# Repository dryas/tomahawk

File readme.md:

# Tomahawk
Tomahawk is a fully open source hardware Bitcoin ASIC miner. It is based on the ideas of Bitaxe by Skot and the Open Source Miners United but a complete redesign with some different components. It includes a BM1366 ASIC which is also used in the Antminer S19XP.

DO NOT USE - WORK IN PROGRESS!

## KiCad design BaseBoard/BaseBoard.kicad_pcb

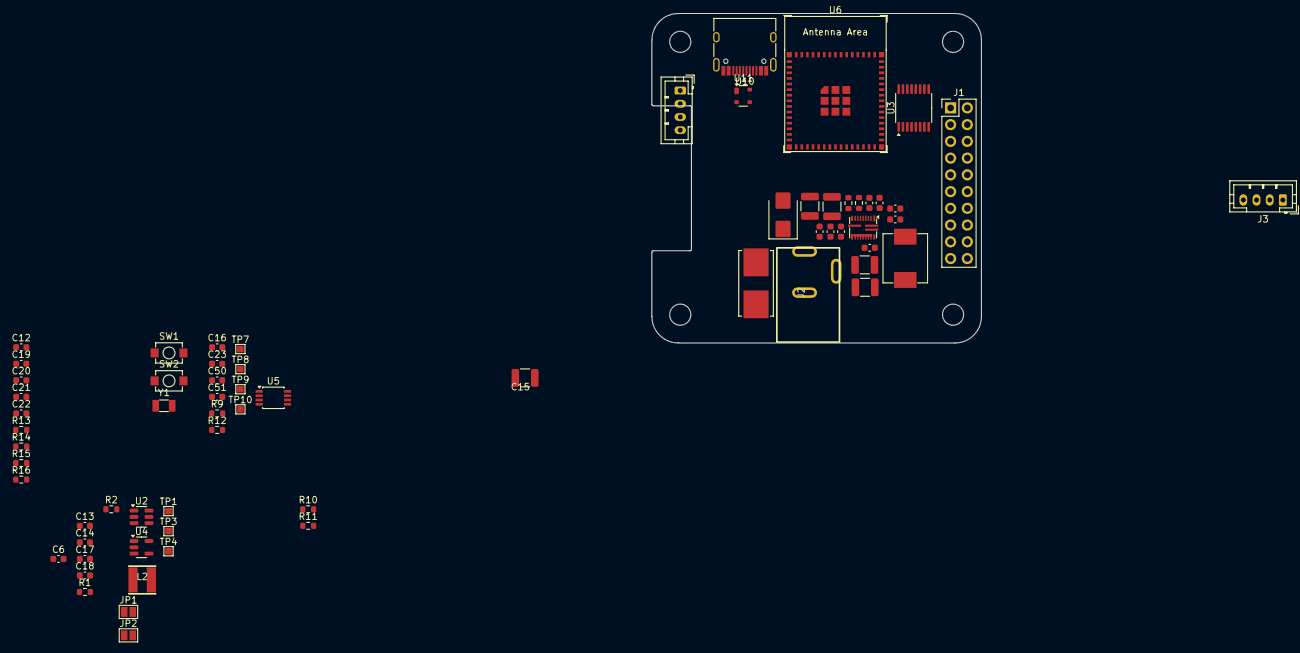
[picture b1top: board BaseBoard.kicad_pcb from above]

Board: 4 copper layers, 50.0 x 50.0 mm, 71 parts (0 on the bottom side), 39 nets, no tracks yet.

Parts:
C1, C2: 22uF; C_1210_3225Metric
C3, C4, C5, C12, C17: 1uF; C_0603_1608Metric
C6, C18: 4.7uF; C_0603_1608Metric
C7: 2.2uF; C_0603_1608Metric
C8: 120nF; C_0603_1608Metric
C9, C13, C16, C22, C23, C50: 100nF; C_0603_1608Metric
C10, C11: 100uF / 6,3V; C_1210_3225Metric
C14: 47pF; C_0603_1608Metric
C15: 47uF; C_1210_3225Metric
C19, C20: 6.8pF; C_0603_1608Metric
C21: 10uF; C_0603_1608Metric
C51: 470pF; C_0603_1608Metric
D1: SMBJ12A; D_SMB
F1: 2A; Fuseholder_Littelfuse_Nano2_154x
H1, H2, H3, H4: MountingHole; MountingHole_3.2mm_M3
J1: Conn_02x10_Odd_Even; PinHeader_2x10_P2.54mm_Vertical
J2: 54-00167
J3: SSD1306 OLED Display; JST_PH_B4B-PH-K_1x04_P2.00mm_Vertical
J4: FAN; JST_PH_B4B-PH-K_1x04_P2.00mm_Vertical
JP1, JP2: SolderJumper-2_P1.3mm_Open_Pad1.0x1.5mm
L1: 200nH / 23A; IND-SMD_L7.3-W6.6
L2: 6.8uH; IND-SMD_L4.1-W4.1
R1: 100k/1%; R_0603_1608Metric
R2: 22.1k/1%; R_0603_1608Metric
R3: 60.4k; C_0603_1608Metric
R4: 4.02k/1%; C_0603_1608Metric
R6: 10.7k/1%; R_0603_1608Metric
R7: 10k/1%; R_0603_1608Metric
R9, R12, R13, R14, R15, R16: 4.7k; R_0603_1608Metric
R10, R11: 5.1K; R_0603_1608Metric
SW1, SW2: SW_Push; TS-1088R-02526
TP1: +1.2V; TestPoint_Pad_1.0x1.0mm
TP3: +3.3V; TestPoint_Pad_1.0x1.0mm
TP4: +0.8V; TestPoint_Pad_1.0x1.0mm
TP7: TEMP_P; TestPoint_Pad_1.0x1.0mm
TP8: TEMP_N; TestPoint_Pad_1.0x1.0mm
TP9: FAN_PWM; TestPoint_Pad_1.0x1.0mm
TP10: FAN_TACH; TestPoint_Pad_1.0x1.0mm
U1: TPS548A28
U2: TPS54202DDC; SOT-23-6
U3: SN74AVC4T774; TSSOP-16_4.4x5mm_P0.65mm
U4: RT9078N-08GJ5; TSOT-23-5
U5: EMC2101; TSSOP-8_3x3mm_P0.65mm
U6: ESP32-S3-MINI-1
U10: USB Type C; USB_C_Receptacle_HRO_TYPE-C-31-M-12
U11: PRTR5V0U2X; SOT-143
Y1: 32.768kHz; Crystal_SMD_3215-2Pin_3.2x1.5mm

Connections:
+1V2: J1.15, J1.16, J1.17, J1.18, J1.19, J1.20
/IO/+1V2: C16.2, U3.7 (DIR3), U3.8 (DIR4), U3.16 (VCCA)
/IO/+3V3: C23.2, C50.2, R9.2, R12.2, U3.15 (VCCB), U5.1 (VDD)
/IO/FAN_PWM: R9.1, TP9.1, U5.4 (FAN)
/IO/FAN_TACH: R12.1, TP10.1, U5.6 (ALERT/TACH)
/IO/TEMP_N: C51.1, TP8.1, U5.3 (DN)
/IO/TEMP_P: C51.2, TP7.1, U5.2 (DP)
/MPU/+1V2: JP1.2 (B), R16.2
/MPU/+3v3: C17.2, C21.2, C22.2, J3.2, JP2.1 (A), R13.2, R14.2, U4.1 (IN), U4.3 (EN), U6.3 (3V3)
/MPU/Enable: R15.2, U6.14 (GPIO10/TOUCH10/ADC1_CH9/FSPICS0/FSPIIO4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)
/MPU/PGOOD: R13.1, U6.15 (GPIO11/TOUCH11/ADC2_CH0/FSPID/FSPIIO5/S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)
/MPU/SCL: J3.3, U6.30 (GPIO48/SPICLK_N/SUBSPICLK_N_DIFF)
/MPU/SDA: J3.4, U6.27 (GPIO47/SPICLK_P/SUBSPICLK_P_DIFF)
/MPU/USB+: U6.24 (GPIO20/U1CTS/ADC2_CH9/CLK_OUT1/USB_D+), U10.A6 (D+), U10.B6 (D+), U11.2
/MPU/USB-: U6.23 (GPIO19/U1RTS/ADC2_CH8/CLK_OUT2/USB_D-), U10.A7 (D-), U10.B7 (D-), U11.3
/MPU/XIN32: C19.2, U6.19 (GPIO15/U0RTS/ADC2_CH4/XTAL_32K_P), Y1.1
/MPU/XOUT32: C20.2, U6.20 (GPIO16/U0CTS/ADC2_CH5/XTAL_32K_NH5), Y1.2
/Power/+0V8: C6.2, TP4.1, U4.4 (SNS), U4.5 (OUT)
/Power/+12V: C1.1, C2.1, C3.1, C4.1, C5.1, C18.2, D1.1 (K), F1.2, U1.10 (VIN), U1.21 (VIN), U2.3 (VIN)
GND: C1.2, C2.2, C3.2, C4.2, C5.2, C6.1, C7.2, C8.2, C10.2, C11.2, C12.2, C15.1, C16.1, C17.1, C18.1, C19.1, C20.1, C21.1, C22.1, C23.1, C50.1, D1.2 (A), J1.2, J1.4, J1.6, J1.8, J1.10, J1.12, J1.14, J2.2, J2.3, J3.1, R2.2, R3.2, R4.2, R7.2, R10.1, R11.1, R15.1, SW1.1, SW2.1, U1.2 (AGND), U1.6 (VSNS-), U1.11 (PGND), U2.1 (GND), U3.1 (DIR1), U3.2 (DIR2), U3.6 (A4), U3.9 (OE), U3.10 (GND), U4.2 (GND), U5.5 (GND), U6.1 (GND), U6.2 (GND), U6.42 (GND), U6.43 (GND), U6.46 (GND), U10.A1 (GND), U10.A12 (GND), U10.B1 (GND), U10.B12 (GND), U10.S1 (SHIELD), U11.1
unnamed: F1.1, J2.1
unnamed: C10.1, C11.1, JP1.1 (A), L1.2, R6.1, TP1.1
unnamed: C14.2, C15.2, JP2.2 (B), L2.2, R1.1, TP3.1
unnamed: C9.1, U1.1 (BOOT)
unnamed: R6.2, R7.1, U1.7 (FB)
unnamed: R3.1, U1.4 (MODE)
unnamed: C8.1, U1.5 (SS/REFIN)
unnamed: C9.2, L1.1
unnamed: R4.1, U1.3 (TRIP)
unnamed: C7.1, U1.19 (VCC)
unnamed: C13.1, U2.6 (BOOT)
unnamed: C14.1, R1.2, R2.1, U2.4 (FB)
unnamed: C13.2, L2.1, U2.2 (SW)
unnamed: C12.1, R14.1, SW2.2, U6.45 (EN)
unnamed: SW1.2, U6.4 (GPIO0/BOOT)
unnamed: R16.1, U6.6 (GPIO2/TOUCH2/ADC1_CH1)
unnamed: R11.2, U10.A5 (CC1)
unnamed: R10.2, U10.B5 (CC2)
unnamed: U10.A4 (VBUS), U10.A9 (VBUS), U10.B4 (VBUS), U10.B9 (VBUS), U11.4

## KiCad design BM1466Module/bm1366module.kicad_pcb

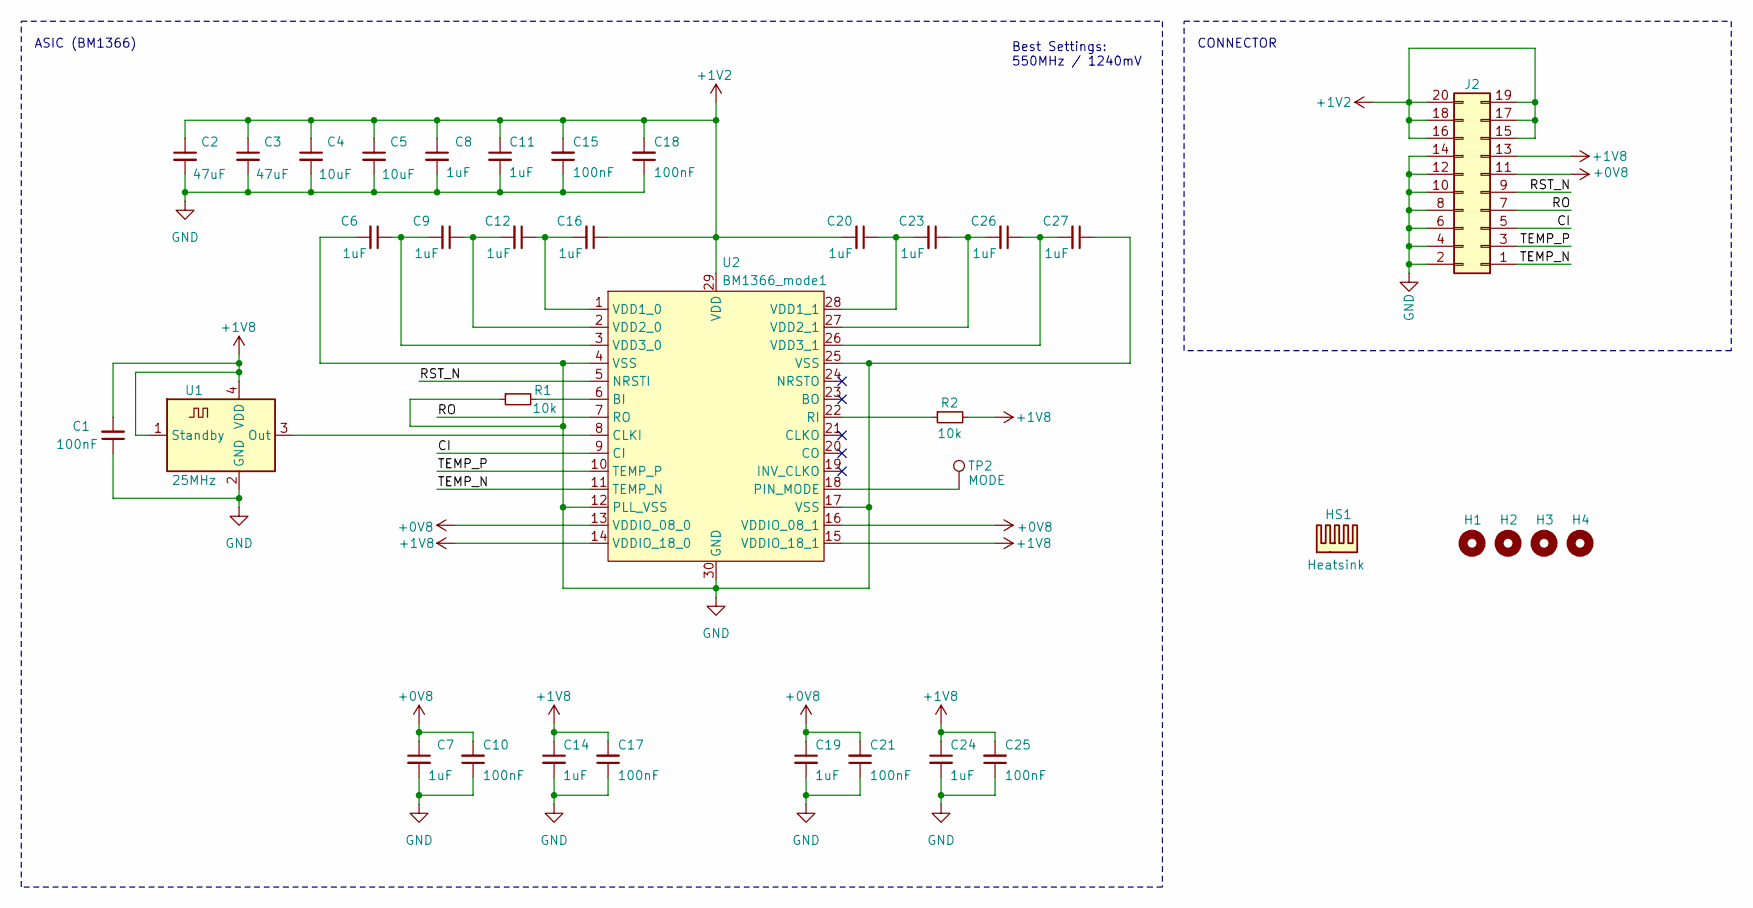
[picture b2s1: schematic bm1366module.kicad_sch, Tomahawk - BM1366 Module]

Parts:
C1, C10, C15, C17, C18, C21, C25: 100nF; C_0603_1608Metric; LCSC C42998
C2, C3: 47uF; C_1206_3216Metric; LCSC C96123
C4, C5: 10uF; C_1206_3216Metric; LCSC C157351
C6, C7, C8, C9, C11, C12, C14, C16, C19, C20, C23, C24, C26, C27: 1uF; C_0603_1608Metric; LCSC C1592
H1, H2, H3, H4: MountingHole; MountingHole_3.2mm_M3
HS1: Heatsink
J2: Conn_02x10_Odd_Even; PinSocket_2x10_P2.54mm_Vertical
R1, R2: 10k; R_0603_1608Metric; LCSC C25804
TP2: MODE; TestPoint_Pad_1.0x1.0mm
U1: 25MHz; Crystal_SMD_3225-4Pin_3.2x2.5mm; LCSC C20617587
U2: BM1366_mode1; BM1366

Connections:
+0V8: C7.1, C10.2, C19.1, C21.2, J2.11, U2.13 (VDDIO_08_0), U2.16 (VDDIO_08_1)
+1V2: C2.1, C3.1, C4.1, C5.1, C8.1, C11.1, C15.2, C16.1, C18.2, C20.2, J2.15, J2.16, J2.17, J2.18, J2.19, J2.20, U2.29 (VDD)
+1V8: C1.2, C14.1, C17.2, C24.1, C25.2, J2.13, R2.2, U1.1 (Standby), U1.4 (VDD), U2.14 (VDDIO_18_0), U2.15 (VDDIO_18_1)
/CI: J2.5, U2.9 (CI)
/RO: J2.7, U2.7 (RO)
/RST_N: J2.9, U2.5 (NRSTI)
/TEMP_N: J2.1, U2.11 (TEMP_N)
/TEMP_P: J2.3, U2.10 (TEMP_P)
GND: C1.1, C2.2, C3.2, C4.2, C5.2, C6.2, C7.2, C8.2, C10.1, C11.2, C14.2, C15.1, C17.1, C18.1, C19.2, C21.1, C24.2, C25.1, C27.1, J2.2, J2.4, J2.6, J2.8, J2.10, J2.12, J2.14, R1.1, U1.2 (GND), U2.4 (VSS), U2.12 (PLL_VSS), U2.17 (VSS), U2.25 (VSS), U2.30 (GND)
unnamed: U1.3 (Out), U2.8 (CLKI)
unnamed: R1.2, U2.6 (BI)
unnamed: TP2.1, U2.18 (PIN_MODE)
unnamed: R2.1, U2.22 (RI)
unnamed: C12.1, C16.2, U2.1 (VDD1_0)
unnamed: C20.1, C23.2, U2.28 (VDD1_1)
unnamed: C9.1, C12.2, U2.2 (VDD2_0)
unnamed: C23.1, C26.2, U2.27 (VDD2_1)
unnamed: C6.1, C9.2, U2.3 (VDD3_0)
unnamed: C26.1, C27.2, U2.26 (VDD3_1)

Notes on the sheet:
Best Settings: 550MHz / 1240mV
CONNECTOR
ASIC (BM1366)

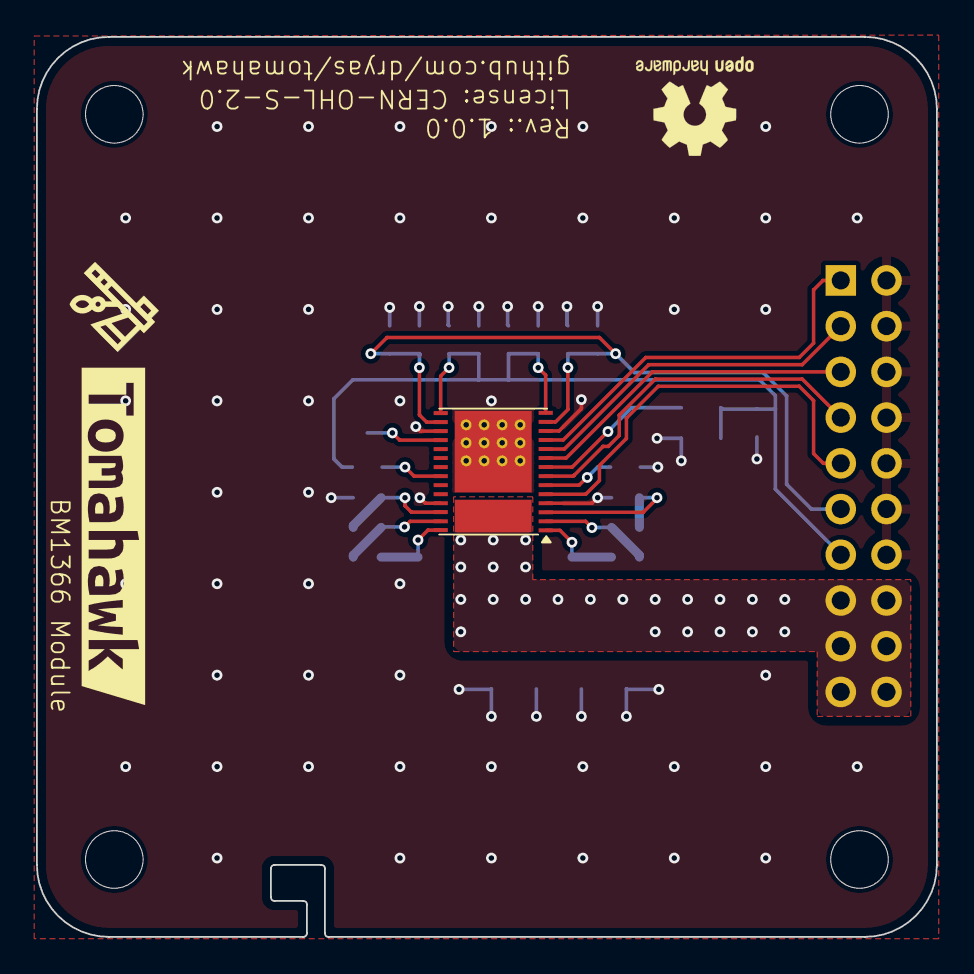
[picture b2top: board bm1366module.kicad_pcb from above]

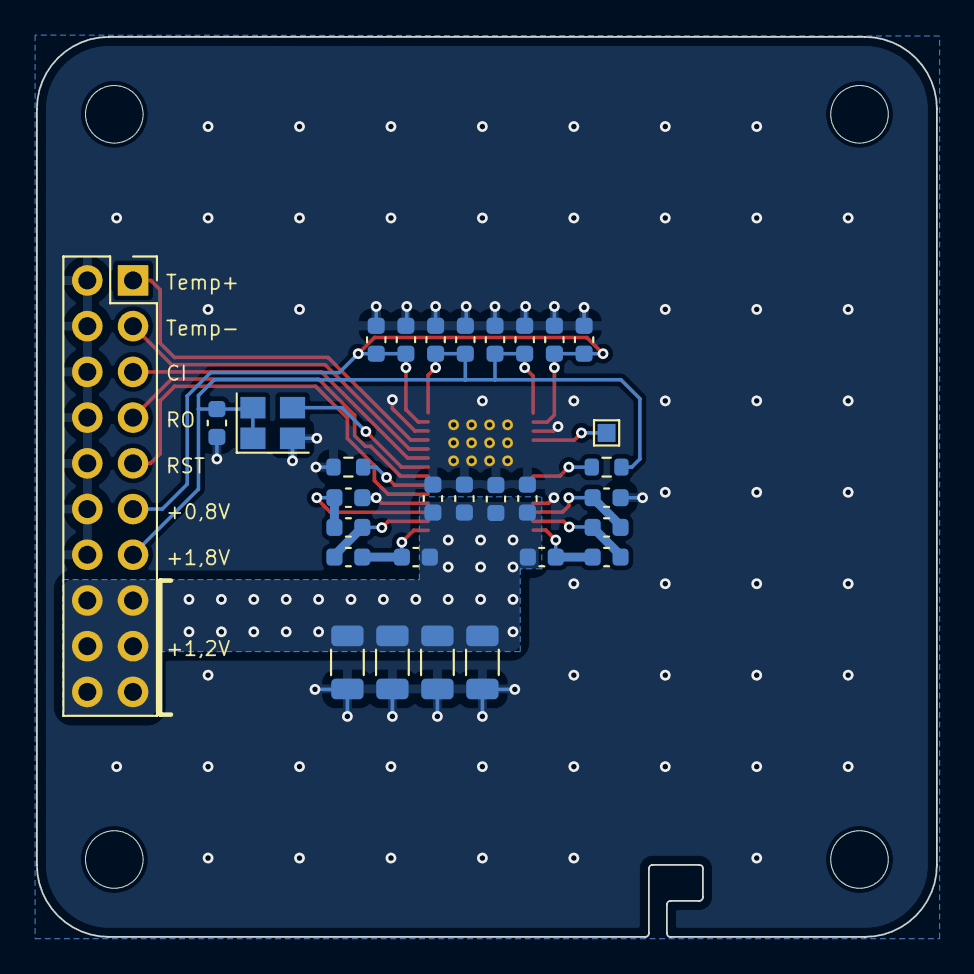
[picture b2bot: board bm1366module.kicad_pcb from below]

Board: 4 copper layers, 50.0 x 50.0 mm, 36 parts (30 on the bottom side), 19 nets.

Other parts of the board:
kibuzzard-677F2641: G***; kibuzzard-677F2641

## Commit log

2025-01-09 Create LICENSE
2025-01-10 Added support for TMP1075 temperature sensor to monitor ASIC
2025-01-10 Directory cleanup
2025-01-10 Add documentation stuff

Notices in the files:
BM1466Module/bm1366module.kicad_pcb:
License: CERN-OHL-S-2.0
